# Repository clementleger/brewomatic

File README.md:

# Disclaimer

I am not experienced with brewing so, be indulgent with what you could found in the following explanations.

# Why ?

While trying to make my own brewing system, I did not find any easy to use and well explained system for small brewing setup.
OpenArdBir code is not well architectured and does not support a full featured screen or an SD card.
I wanted a configurable system to match user needs.

#  Brew-O-Matic

Brew-O-Matic aims to be an easy to use brewing system for really (really (really)) small  all-in-one brewing setup.
It contains the following features:
* Temperature probes:
 * PT100 via MAX31865
 * DS18B20
* Input
 * Rotary Encoder
* LCD support
 * LCD2004 (Discount Controller)
 * ILI9341 (via uCglig, incomplete support)
* Pump control via MOSFET
* Heating element support
 * 50/60Hz main automatic detection
 * PID controlled heating
* Beeper
* Internationalization

Some feature can be opt out such as beeper and sd card.
Others can be choosen according to your hardware

## Design

BrewOMatic is designed to easily add a temperature sensor, input, display, etc.

## Adding a language

Languages support can easily be added. You simply have to add a Lang<YourLanguage>.h file to the lang directory.
To do that, simply recopy the LangEnglish.h file and translate the existing strings.
Be careful not to reorder entries ! (tech hint: gcc-avr does not support designated initializer)

# Building

## Configuration

In order to configure BrewOMatic to suit your configuration, you can modify Config.h
All options are clearly documented. The default configuration suit the custom brewing controller.

## Needed libraries

Depending on your configuration, you will need the following libraries:
* SD
* PIDv1
* LiquidCrystal
* TimerOne
* uCGlib
* Rotary Encoder
* TempDS18B20

## Command

Using and arduino ide, load the BrewOMatic.ino file into the IDE.
Compile it and upload it to the arduino.

# Usage

It is advised to use a SD card to store recipe easily

## Modes

### Manual mode

When in manual, mode, user can control pump, temperature

### Recipe execution

In order to execute a recipe, go Browse SD card.

## Recipe format

Recipes are stored in .br (Brew Recipe) files on SD card.
The format is basically a csv files with specific values:

Lines format is the following:
step;duration;temperature;pump_enable;pump_duty_cycle

Step is mainly an indicator to display the correct step name on LCD.
Step can be one of the following value:
 - H: Heating step
 - M: Mashing step
 - B: Boiling step
 - C: Cooling

Duration is then the step duration described in minutes.
Temperature is the target temperature for this phase in Celsius.
And finally pump_enable is a boolean describing if pump should be enabled for the
step. pump_duty_cycle is the duty cycle (0% - 100%) for the pump (done using PWM).

For instance, the following line tell the system that we are in a heating step for 10 minutes
and that the expected temperature is 70 degrees celsius:

H;10;70;1

Additionnaly to these main steps, some actions can be added using the following syntax:
A;action_type;time

Action type can be on of the following value:
 - I: Insert malt
 - R: Remove malt
 - C: Setup Cooler
 - H: Insert Hop
 - V: Verify everything !

If time is is equal -1, then, the action will be executed before the step.
The action must also be put before the step line in the recipe.

Check the recipe folder for some samples recipes !

# Hardware

A kicad pcb is available which contains support for 20A load control, pump and LCD 2004 support (such as for 3D printer).
The main components needed to control the brewing system are the following
* Arduino
* TRIAC for heater
* MOSFET for pump

The PCB is provided as an example configuration and I am not responsible of any damages you could have.

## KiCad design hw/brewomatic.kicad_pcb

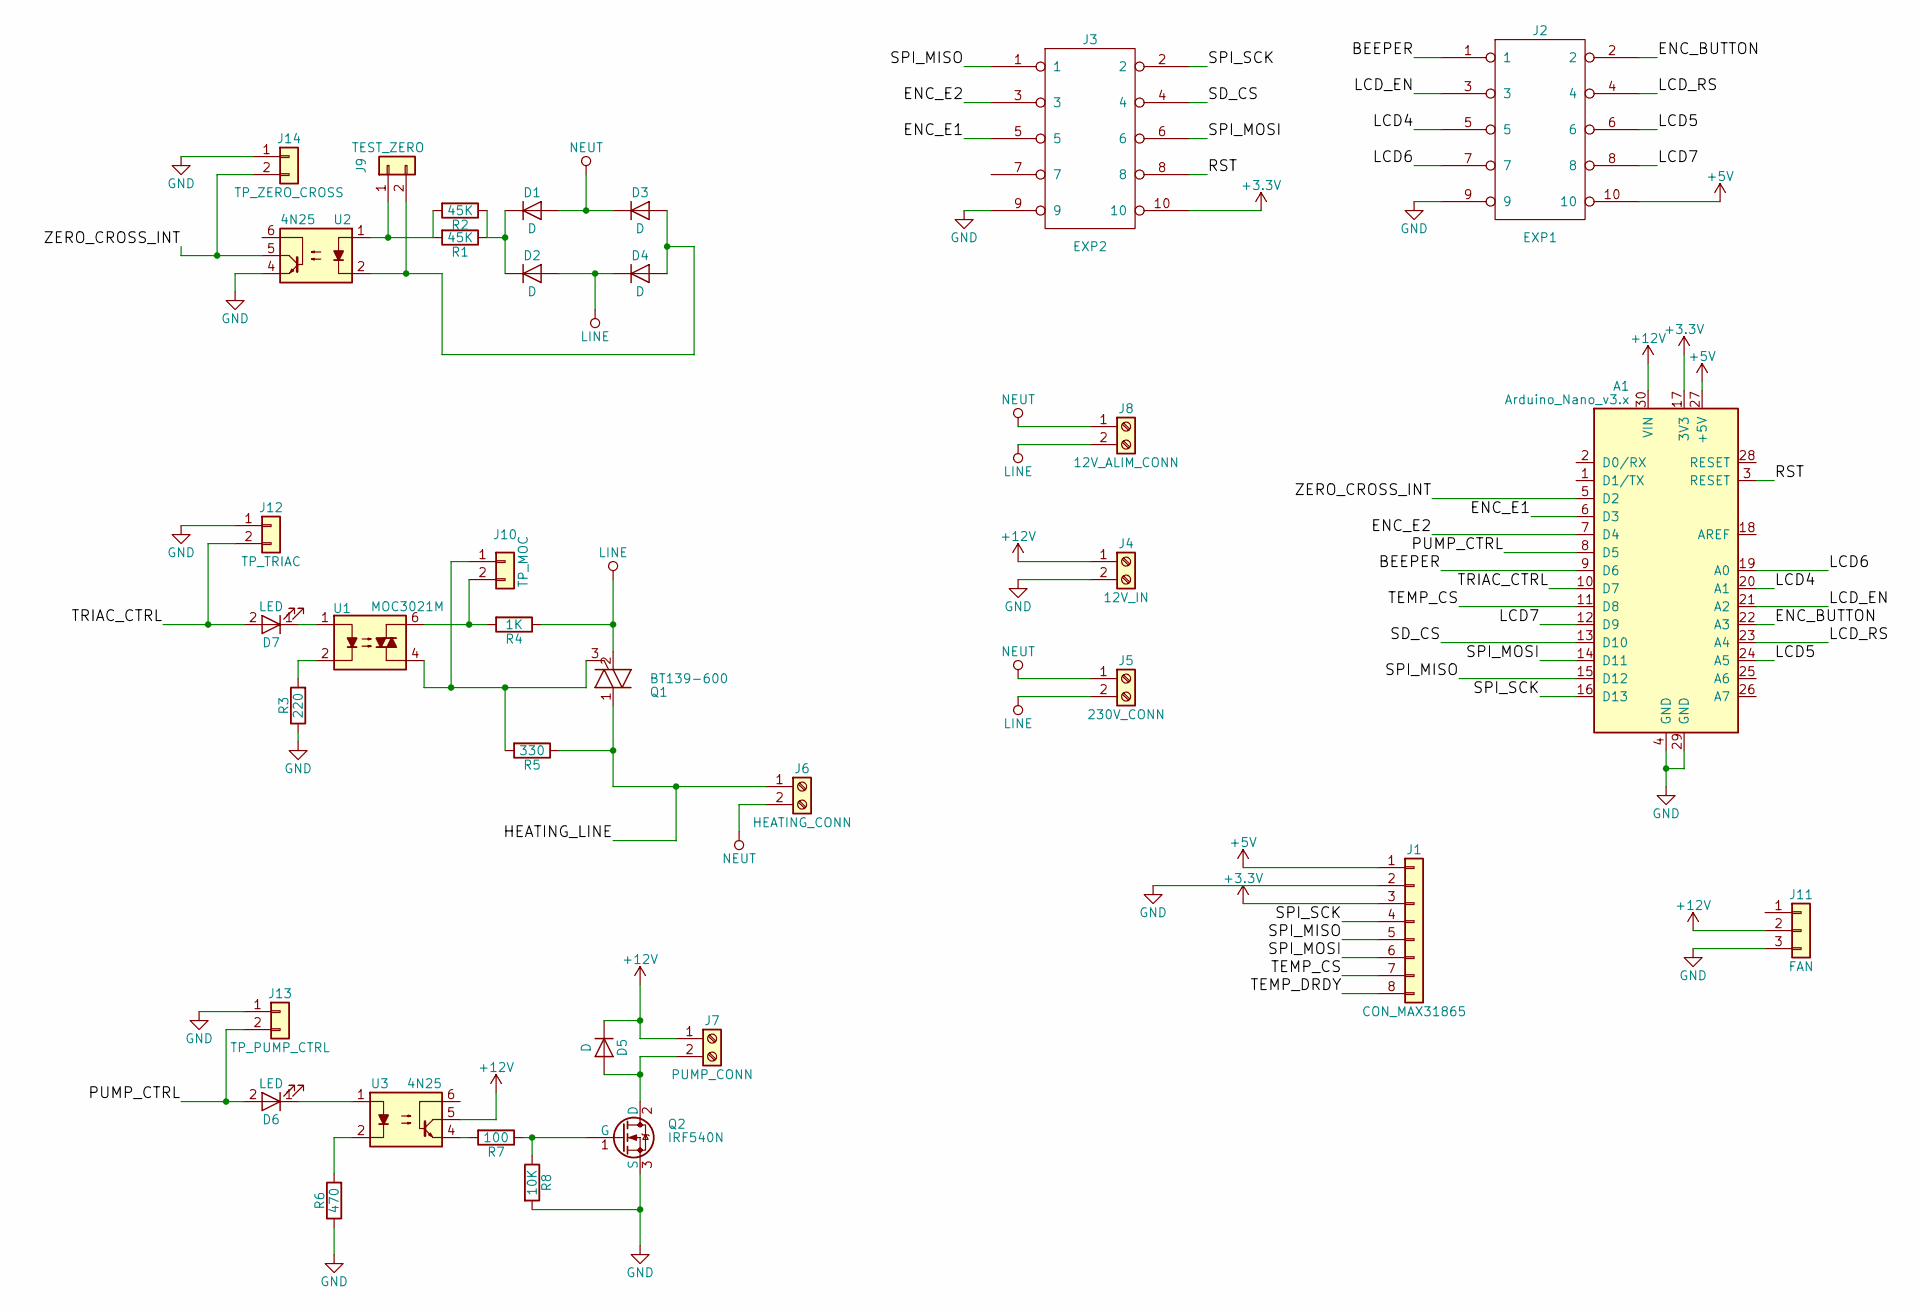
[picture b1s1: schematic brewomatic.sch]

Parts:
A1: Arduino_Nano_v3.x; Arduino_Nano
D1, D2, D3, D4, D5: D; D_T-1_P10.16mm_Horizontal
D6, D7: LED; LED_D5.0mm
J1: CON_MAX31865; Pin_Header_Straight_1x08_Pitch2.54mm
J2: EXP1; Pin_Header_Straight_2x05_Pitch2.54mm
J3: EXP2; Pin_Header_Straight_2x05_Pitch2.54mm
J4: 12V_IN; TerminalBlock_bornier-2_P5.08mm
J5: 230V_CONN; TerminalBlock_bornier-2_P5.08mm
J6: HEATING_CONN; TerminalBlock_bornier-2_P5.08mm
J7: PUMP_CONN; TerminalBlock_bornier-2_P5.08mm
J8: 12V_ALIM_CONN; TerminalBlock_bornier-2_P5.08mm
J9: TEST_ZERO; Pin_Header_Straight_1x02_Pitch2.54mm
J10: TP_MOC; Pin_Header_Straight_1x02_Pitch2.54mm
J11: FAN; Pin_Header_Straight_1x03_Pitch2.54mm
J12: TP_TRIAC; Pin_Header_Straight_1x02_Pitch2.54mm
J13: TP_PUMP_CTRL; Pin_Header_Straight_1x02_Pitch2.54mm
J14: TP_ZERO_CROSS; Pin_Header_Straight_1x02_Pitch2.54mm
Q1: BT139-600; TO-220_Vertical_HV
Q2: IRF540N; TO-220_Vertical
R1, R2: 45K; R_Axial_DIN0207_L6.3mm_D2.5mm_P10.16mm_Horizontal
R3: 220; R_0805_HandSoldering
R4: 1K; R_Axial_DIN0207_L6.3mm_D2.5mm_P10.16mm_Horizontal
R5: 330; R_Axial_DIN0207_L6.3mm_D2.5mm_P10.16mm_Horizontal
R6: 470; R_0805_HandSoldering
R7: 100; R_0805_HandSoldering
R8: 10K; R_0805_HandSoldering
U1: MOC3021M; DIP-6_W7.62mm_Socket
U2, U3: 4N25; DIP-6_W7.62mm_Socket

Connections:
+3V3: A1.17 (3V3), J1.3, J3.10
+5V: A1.27 (+5V), J1.1, J2.10
+12V: A1.30 (VIN), D5.1 (K), J4.1, J7.1, J11.2, U3.5
/BEEPER: A1.9 (D6), J2.1
/ENC_BUTTON: A1.22 (A3), J2.2
/ENC_E1: A1.6 (D3), J3.5
/ENC_E2: A1.7 (D4), J3.3
/HEATING_LINE: J6.1, Q1.1 (A1), R5.1
/LCD4: A1.20 (A1), J2.5
/LCD5: A1.24 (A5), J2.6
/LCD6: A1.19 (A0), J2.7
/LCD7: A1.12 (D9), J2.8
/LCD_EN: A1.21 (A2), J2.3
/LCD_RS: A1.23 (A4), J2.4
/PUMP_CTRL: A1.8 (D5), D6.2 (A), J13.2
/RST: A1.3 (RESET), J3.8
/SD_CS: A1.13 (D10), J3.4
/SPI_MISO: A1.15 (D12), J1.5, J3.1
/SPI_MOSI: A1.14 (D11), J1.6, J3.6
/SPI_SCK: A1.16 (D13), J1.4, J3.2
/TEMP_CS: A1.11 (D8), J1.7
/TEMP_DRDY: J1.8
/TRIAC_CTRL: A1.10 (D7), D7.2 (A), J12.2
/ZERO_CROSS_INT: A1.5 (D2), J14.2, U2.5
GND: A1.4 (GND), A1.29 (GND), J1.2, J2.9, J3.9, J4.2, J11.3, J12.1, J13.1, J14.1, Q2.3 (S), R3.1, R6.1, R8.2, U2.4
LINE: D2.2 (A), D4.1 (K), J5.2, J8.2, Q1.2 (A2), R4.1
NEUT: D1.2 (A), D3.1 (K), J5.1, J6.2, J8.1
unnamed: D1.1 (K), D2.1 (K), R1.1, R2.1
unnamed: D3.2 (A), D4.2 (A), J9.2, U2.2
unnamed: D5.2 (A), J7.2, Q2.2 (D)
unnamed: D6.1 (K), U3.1
unnamed: D7.1 (K), U1.1
unnamed: J9.1, R1.2, R2.2, U2.1
unnamed: J10.1, Q1.3 (G), R5.2, U1.4
unnamed: J10.2, R4.2, U1.6
unnamed: Q2.1 (G), R7.1, R8.1
unnamed: R3.2, U1.2
unnamed: R6.2, U3.2
unnamed: R7.2, U3.4

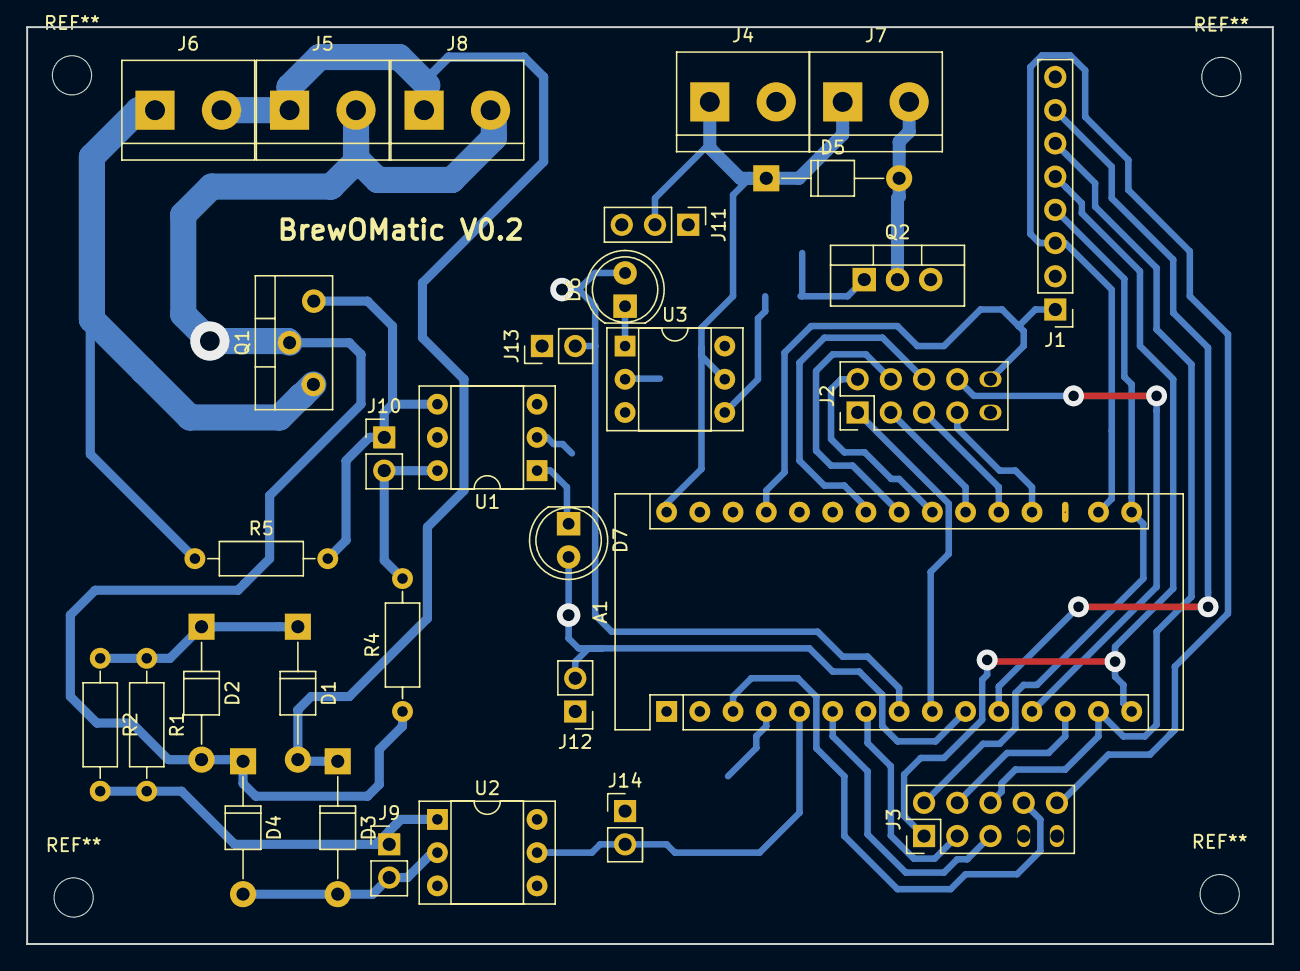
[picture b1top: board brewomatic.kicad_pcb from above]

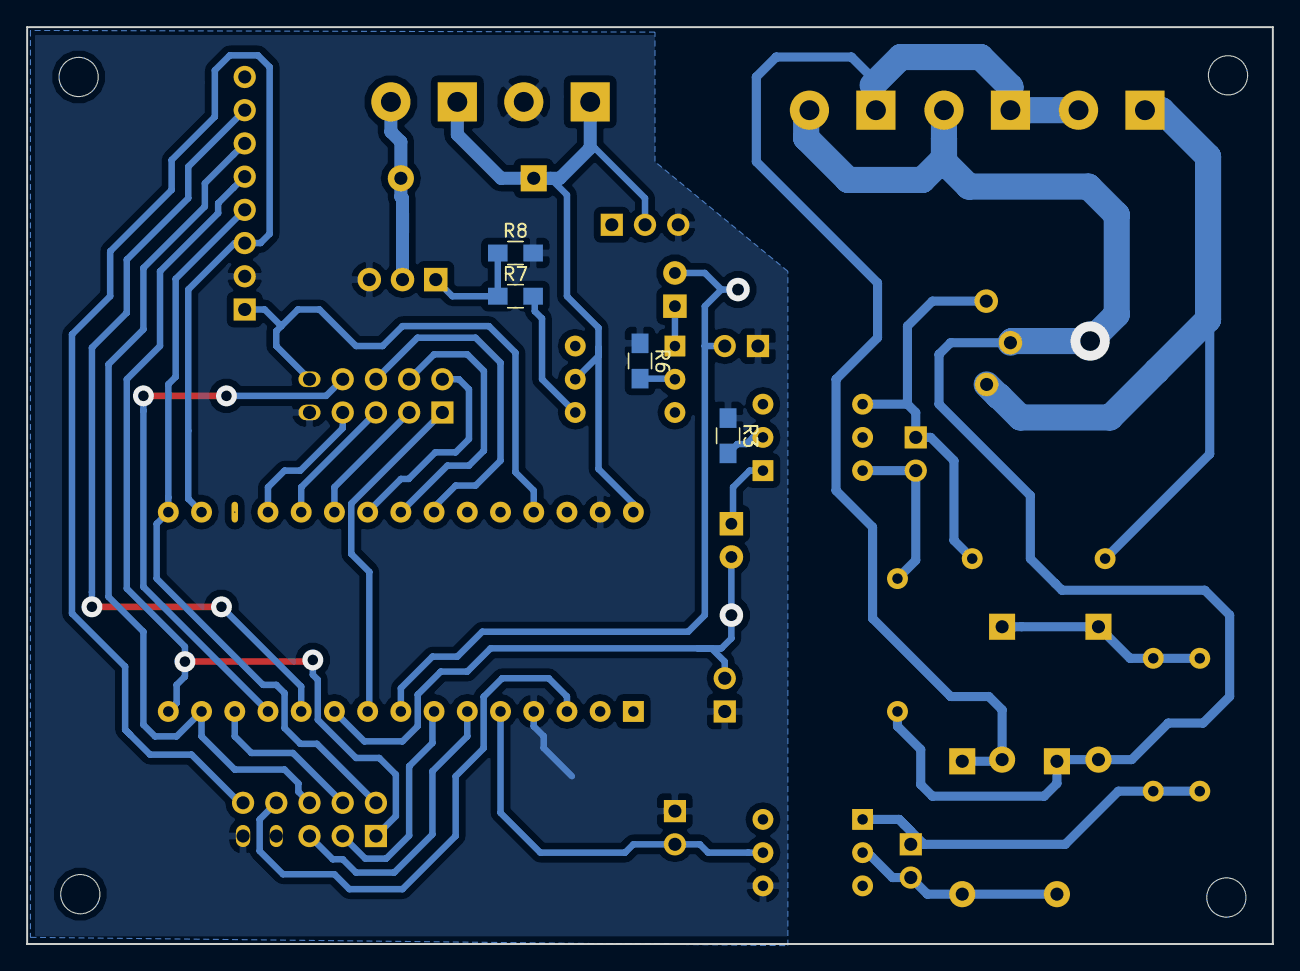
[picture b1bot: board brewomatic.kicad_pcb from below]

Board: 2 copper layers, 95.2 x 70.1 mm, 35 parts (4 on the bottom side), 38 nets.

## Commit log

2018-02-20 Software: add first sources of BrewOmatic
2018-02-21 Add Language handling and Display
    In order to have aconfigurable architecture, handle i18n.
    This is done through string index and language files.
    Add a BrewOMatic and an observer class to easily plug event listener.
2018-02-21 Remove useless file
2018-02-22 Implementation still ongoing !
2018-02-27 Lots of modification (yeah useless commit message...)
2018-03-01 Start recipe execution implementation
2018-03-05 Rework actions and steps
2018-03-06 Continue recipe implementation
2018-03-18 Various fixes of all kind.. can't even find a correct commit message
2018-03-19 Display brewOmatic banner and split List from Recipe to create Menu
2018-03-20 Try to reduce size and fix language
2018-03-24 Implement menu, idle and brewing
2018-03-25 Add hardware schematic
2018-03-25 Handle menu correctly + idle and brewing.
2018-03-25 Start layout of pcb
2018-03-25 WAit fopr target temperature display
2018-03-26 PCB routing done
2018-03-27 Less dangerous schematic !
2018-03-28 PCB: finalize layout
2018-03-30 PCB: fix missing TEMP_CS pin and delete sd_detect
2018-04-03 HW: fix schematic for zero crossing input
2018-04-04 PCB: update and fix LCD7/LCD5 swap
2018-04-05 Fix wrong pcb connection pcb
2018-04-08 Reverse triac terminal since it only works in one direction and fix various problems
2018-04-08 Start implementation of LiquidCrystal
2018-04-09 Implement brewing display completely
2018-04-09 Add 12V fan plug
2018-04-11 Fix display heater, and use PSM to drive AC
2018-04-19 Update recipe for testing and enable temperature sensor.
2018-04-22 Add manual mode
2018-04-22 Fix various problems
    Fix menu update
    Use autoconvert for max31865
    Display PID output value on screen
    Fix stop brewing
2018-04-23 Better handling of enable pump and heater
2018-04-24 Handle menu larger than display height
2018-04-24 Fix heating control by computing pulse to trigger and not pulse to skip
2018-04-24 Various fixes
    - Disable heater in manual mode
    - Remove useless entry from idle menu
    - Remove dbgOutput from Zero Crossing interrupt
    - Remove start delay
2018-04-25 Rework ACZeroCrossing and HeaterControl
2018-04-27 Try to trigger triac interrupt on time...
2018-04-27 HW: Add testpoints on schematic
2018-04-30 Heating: better handling of PWM for AC
2018-04-30 hw: Add testpoints for various input/output
    This is helpful to plug logic analyzer on them
2018-04-30 BrewOmatic: factorize code and add constructor
2018-04-30 LiquidCrystal: offset display by 1 row to display status messages
2018-05-02 Rework brewomatic state machine
2018-05-02 Fix automaton
2018-05-03 Add sd card preliminary work
    Moreover, remove useless SerialOutput class
2018-05-04 Beeper: inline implementation
2018-05-04 Ongoing implementation of SDcard reading
2018-05-09 Add configurable beeper support
2018-05-09 Better support for SD menu
    Add various MenuItem classes to support multiple storage type.
    This is useful for SDcard menu and submenus.
2018-05-09 Doc: improve documentation
2018-05-10 Option for animated icons to save space + eeprom strings
2018-05-10 ZeroCross: remove early debug return
2018-05-10 Various modifications to save space !
2018-05-13 Remove useless heating enabled option in recipe
2018-05-15 Rework config for temp and display
2018-05-15 Fix warnings and start recipe parsing
2018-05-16 Continue implementation of parsing
2018-05-20 Functionnal recipe parsing from SD card
2018-05-21 Put custom character in progmem
2018-05-21 Add icons for menu
2018-05-21 Fix display glitches
2018-05-21 HeaterControl: fix wrong init values
2018-05-21 DO not use special case for 100% value and protect atomic update of values
2018-05-25 Complete action parsing from recipe
2018-05-25 Add recipe folder
2018-05-25 Handling a maximlum fixed size of recipes to avoid stack overflow
2018-05-25 Display: better handling of icons
2018-06-03 Add statistic output and remove lots of useless new
2018-06-06 Stat: Add stratistic output for temperature
    Add sd card logging and serial output stats.
2018-06-07 Fix heater stopped at end of step
2018-06-10 Statistics: save some precious bytes
    Use itoa which is much smaller than sprintf to avoid wasting memory
2018-06-14 Recipes: add new recipes and change format
    Change action parsing format.
2018-07-24 Add sampling time in start of statistic output
2018-08-13 Fix boiling time of recipe
2018-08-13 Add sample log to creat gnuplot script
2018-08-13 Fix small potential bugs and warning
2018-08-13 Handle pump duty cycle in recipes
2018-08-14 Add gnuplot tracing script to use brew.log files
2018-08-14 Fix pumpset + display of dump
2018-08-15 Fix pump not being stopped when disabled
2018-08-15 Fix wrong number of token parsed
2018-08-15 Fix status being erased
2018-08-15 Remove seconds from total time to display pump power correctly
2018-08-15 Handle manual temp adjustment in recipe mode
2018-08-15 Display only .br recipes
2018-08-15 Fix temperature wrongly displayed on idle menu
2018-09-15 FIrst beer has been brewed, it deserve a 0.2 :D
2018-09-15 Fix wrong target temp (using currentSTepo target instead of BrewOmatic
2018-09-15 Add a new menu entry to go to next step
2018-09-15 Exit menu after going to next step
